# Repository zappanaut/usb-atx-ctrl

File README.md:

# usb-atx-ctrl
Using RP2040-Zero to control ATX operations via USB.

*Populated board attached to old network card bracket (J2 is only connected for debugging!)*

A good fit is the Intel E23237-001 slot bracket.

### HOWTO

This repository is part of my [pikvm-usb-atx-ctrl](https://github.com/zappanaut/pikvm-usb-atx-ctrl) project. For more information please have a look at the aforementioned repository.

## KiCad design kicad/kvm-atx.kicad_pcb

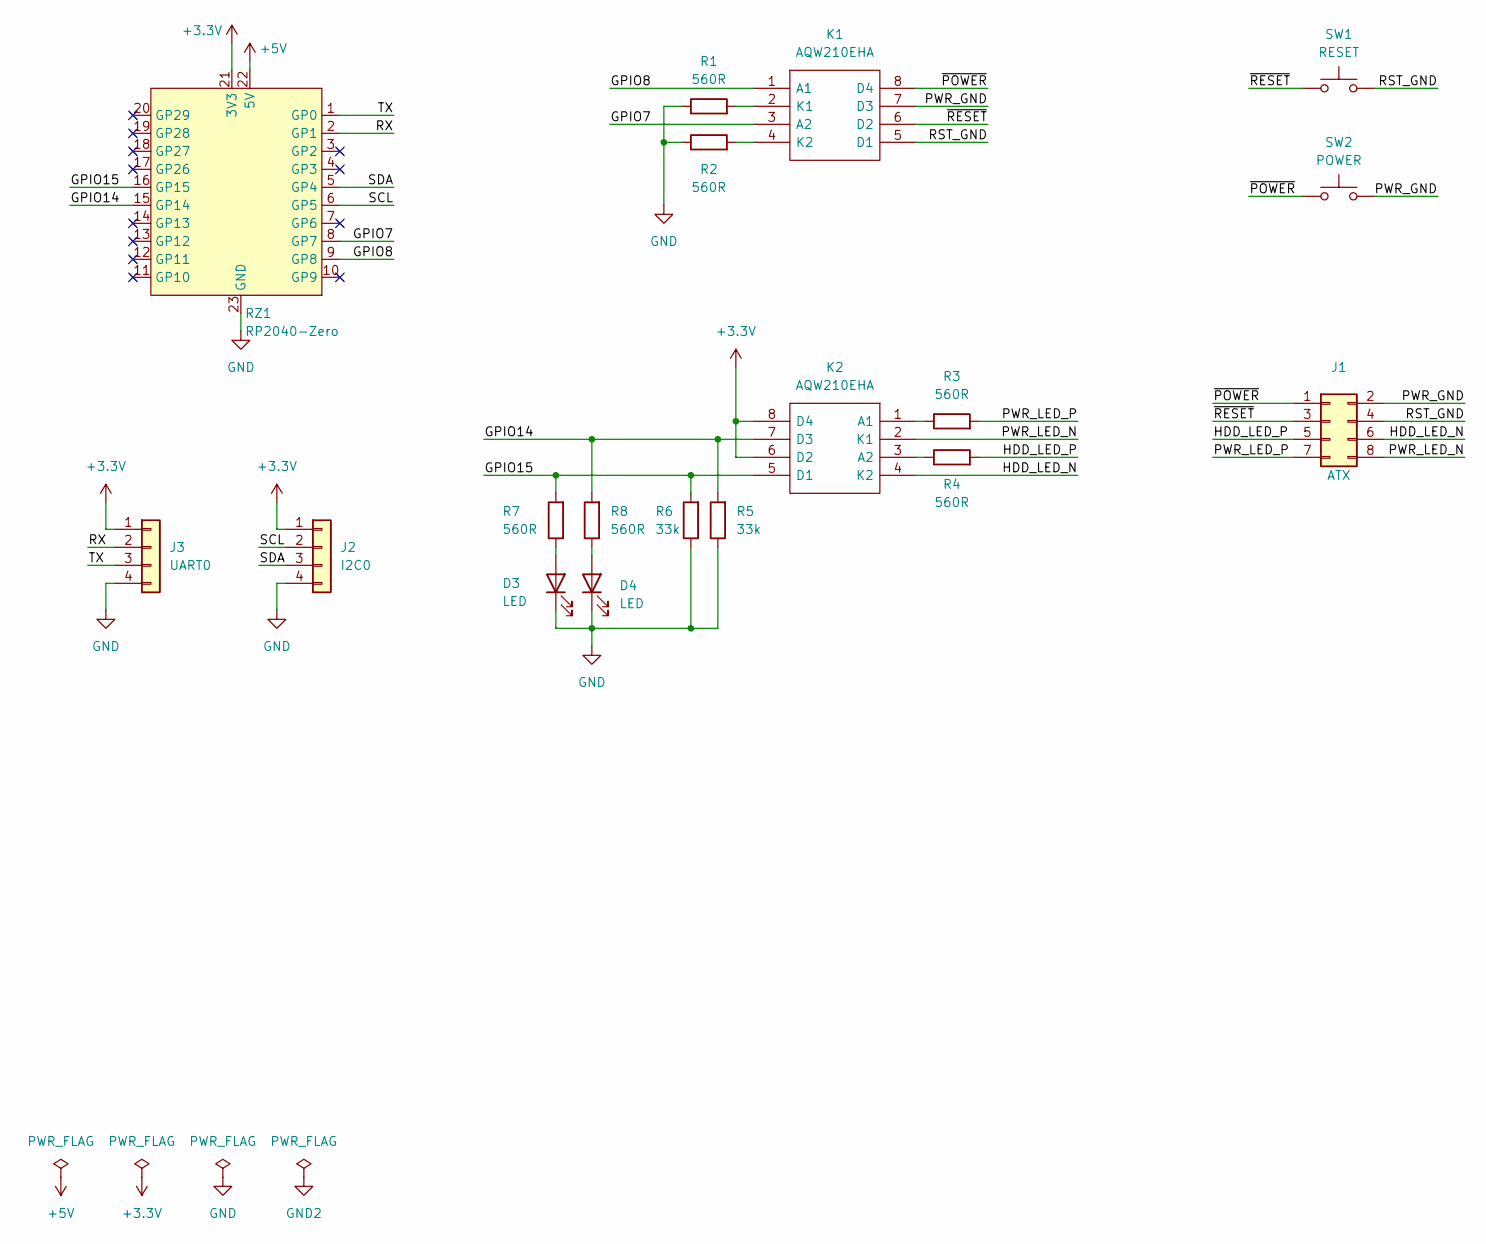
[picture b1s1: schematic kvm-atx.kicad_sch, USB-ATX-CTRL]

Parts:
D3, D4: LED; LED_1206_3216Metric_Pad1.42x1.75mm_HandSolder
J1: ATX; IDC-Header_2x04_P2.54mm_Horizontal
J2: I2C0; PinHeader_1x04_P2.54mm_Vertical
J3: UART0; PinHeader_1x04_P2.54mm_Vertical
K1, K2: AQW210EHA; SOP254P962X315-8N; Manufacturer_Part_Number AQW210EHA; Mouser Part Number 769-AQW210EHA
R1, R2, R3, R4, R7, R8: 560R; R_1206_3216Metric_Pad1.30x1.75mm_HandSolder
R5, R6: 33k; R_1206_3216Metric_Pad1.30x1.75mm_HandSolder
RZ1: RP2040-Zero
SW1: RESET; SW_PUSH_6mm
SW2: POWER; SW_PUSH_6mm

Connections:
+3.3V: J2.1, J3.1, K2.6 (D2), K2.8 (D4), RZ1.21 (3V3)
+5V: RZ1.22 (5V)
/GPIO7: K1.3 (A2), RZ1.8 (GP7)
/GPIO8: K1.1 (A1), RZ1.9 (GP8)
/GPIO14: K2.7 (D3), R5.2, R8.2, RZ1.15 (GP14)
/GPIO15: K2.5 (D1), R6.2, R7.2, RZ1.16 (GP15)
/HDD_LED_N: J1.6, K2.4 (K2)
/HDD_LED_P: J1.5, R4.2
/PWR_GND: J1.2, K1.7 (D3), SW2.2
/PWR_LED_N: J1.8, K2.2 (K1)
/PWR_LED_P: J1.7, R3.2
/RST_GND: J1.4, K1.5 (D1), SW1.2
/RX: J3.2, RZ1.2 (GP1)
/SCL: J2.2, RZ1.6 (GP5)
/SDA: J2.3, RZ1.5 (GP4)
/TX: J3.3, RZ1.1 (GP0)
/~POWER: J1.1, K1.8 (D4), SW2.1
/~RESET: J1.3, K1.6 (D2), SW1.1
GND: D3.1 (K), D4.1 (K), J2.4, J3.4, R1.1, R2.1, R5.1, R6.1, RZ1.23 (GND)
unnamed: D3.2 (A), R7.1
unnamed: D4.2 (A), R8.1
unnamed: K1.2 (K1), R1.2
unnamed: K1.4 (K2), R2.2
unnamed: K2.1 (A1), R3.1
unnamed: K2.3 (A2), R4.1

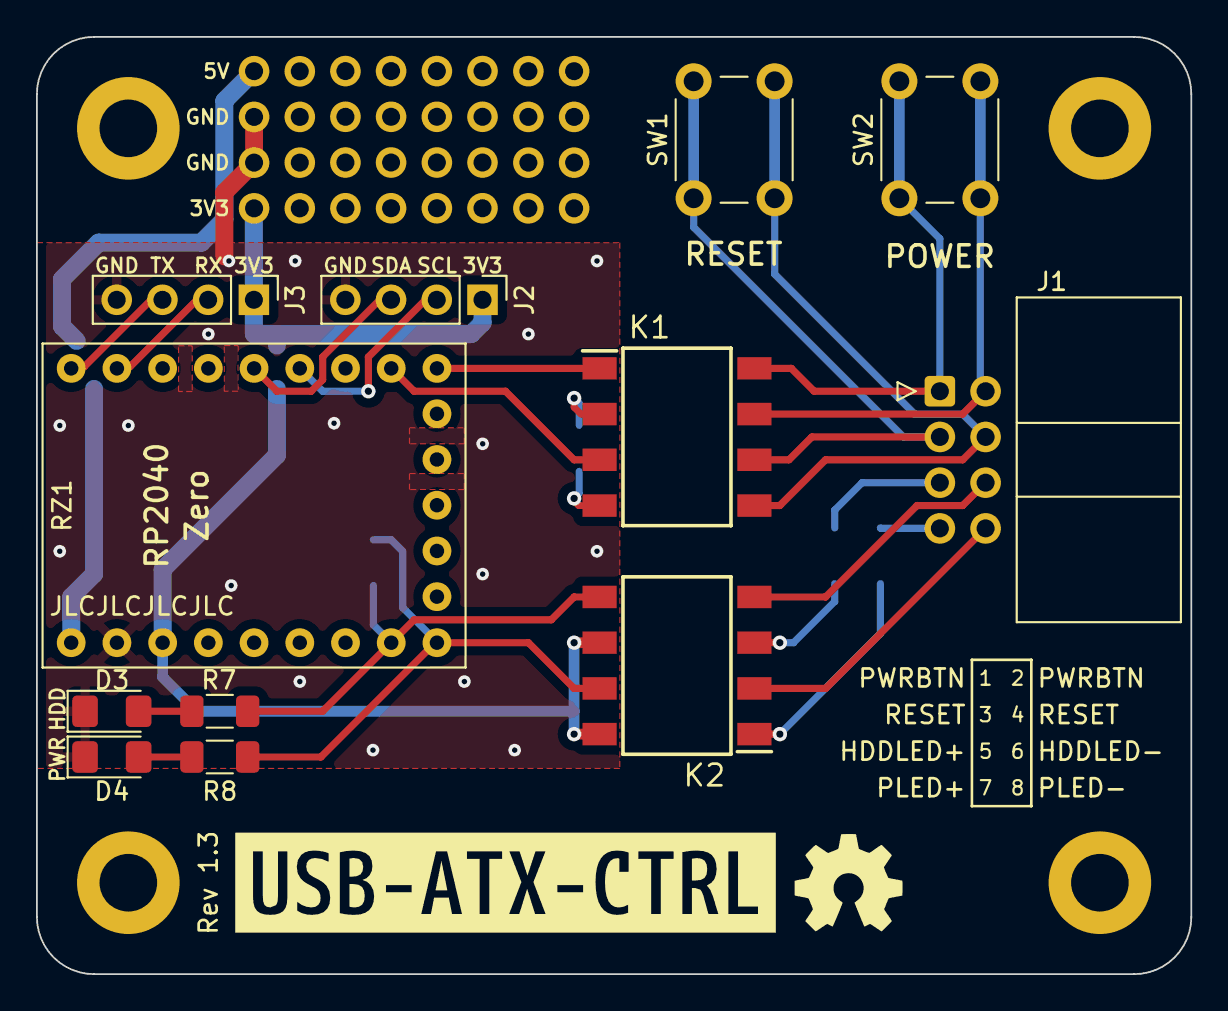
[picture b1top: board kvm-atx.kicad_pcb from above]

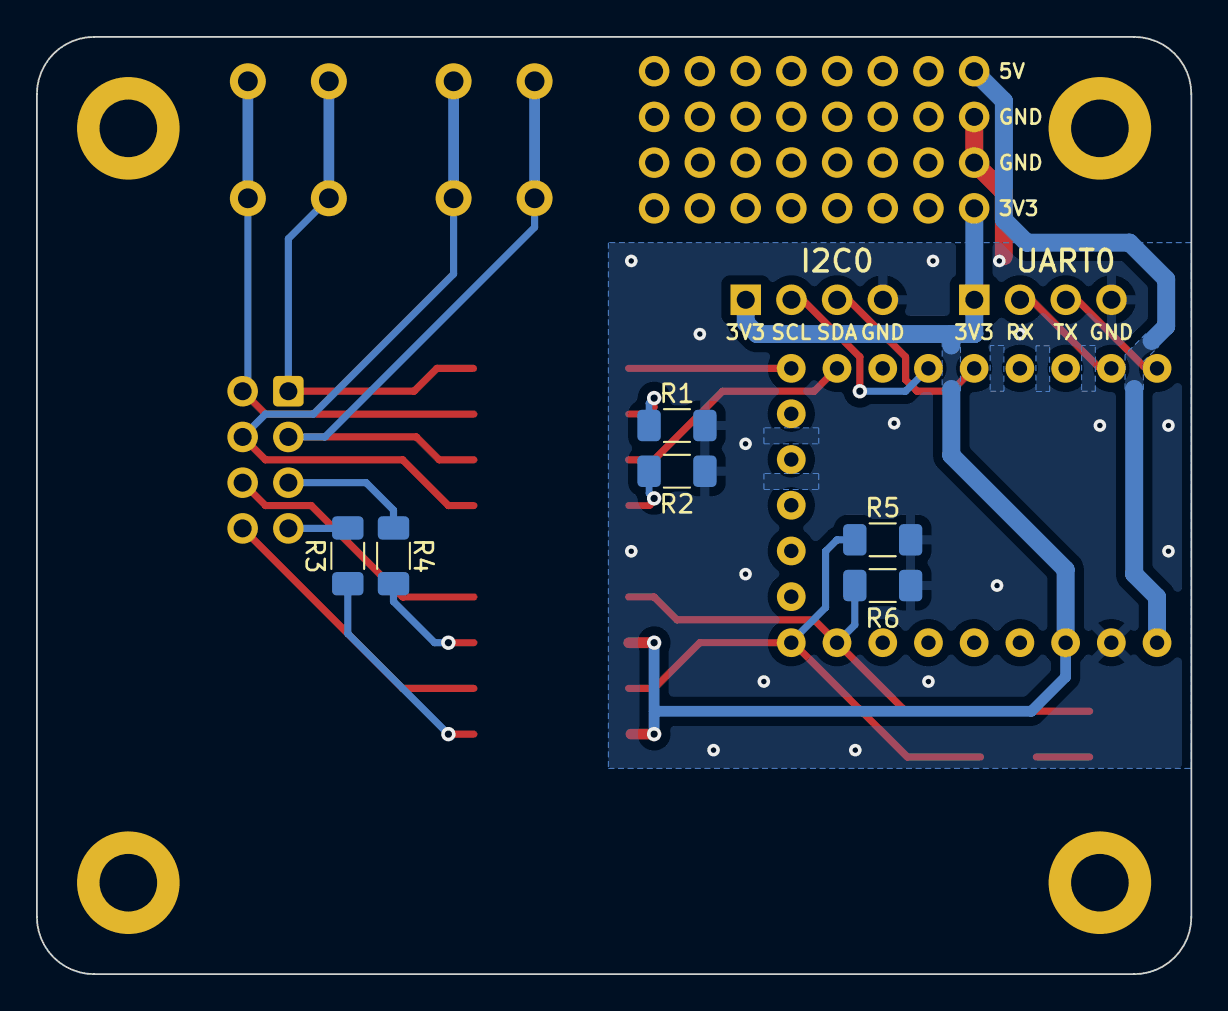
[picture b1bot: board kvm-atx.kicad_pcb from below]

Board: 2 copper layers, 64.1 x 52.1 mm, 20 parts (6 on the bottom side), 24 nets.

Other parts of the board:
G1: LOGO
kibuzzard-639AEF10: G***; kibuzzard-639AEF10

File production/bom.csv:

Designator,Footprint,Quantity,Value,LCSC Part #
D3,1206,1,LED,
D4,1206,1,LED,
J1,IDC-Header_2x04_P2.54mm_Horizontal,1,ATX,
J2,PinHeader_1x04_P2.54mm_Vertical,1,I2C0,
J3,PinHeader_1x04_P2.54mm_Vertical,1,UART0,
"K1, K2",SOP254P962X315-8N,2,AQW210EHA,
R1,1206,1,560R,
R2,1206,1,560R,
R3,1206,1,560R,
R4,1206,1,560R,
R5,1206,1,33k,
R6,1206,1,33k,
R7,1206,1,560R,
R8,1206,1,560R,
RZ1,RP2040-Zero,1,RP2040-Zero,
SW1,SW_PUSH_6mm,1,RESET,
SW2,SW_PUSH_6mm,1,POWER,

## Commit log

2023-01-28 Added KiCAD files
2023-01-28 Added production files (NOT verified but should work).
2023-01-28 Added schematic and PCB rendering
2023-01-30 Added picture of the populated PCB
2023-04-03 Added a simple PCB case.
2024-02-09 better image description
2024-02-09 fixed typo in README.md
